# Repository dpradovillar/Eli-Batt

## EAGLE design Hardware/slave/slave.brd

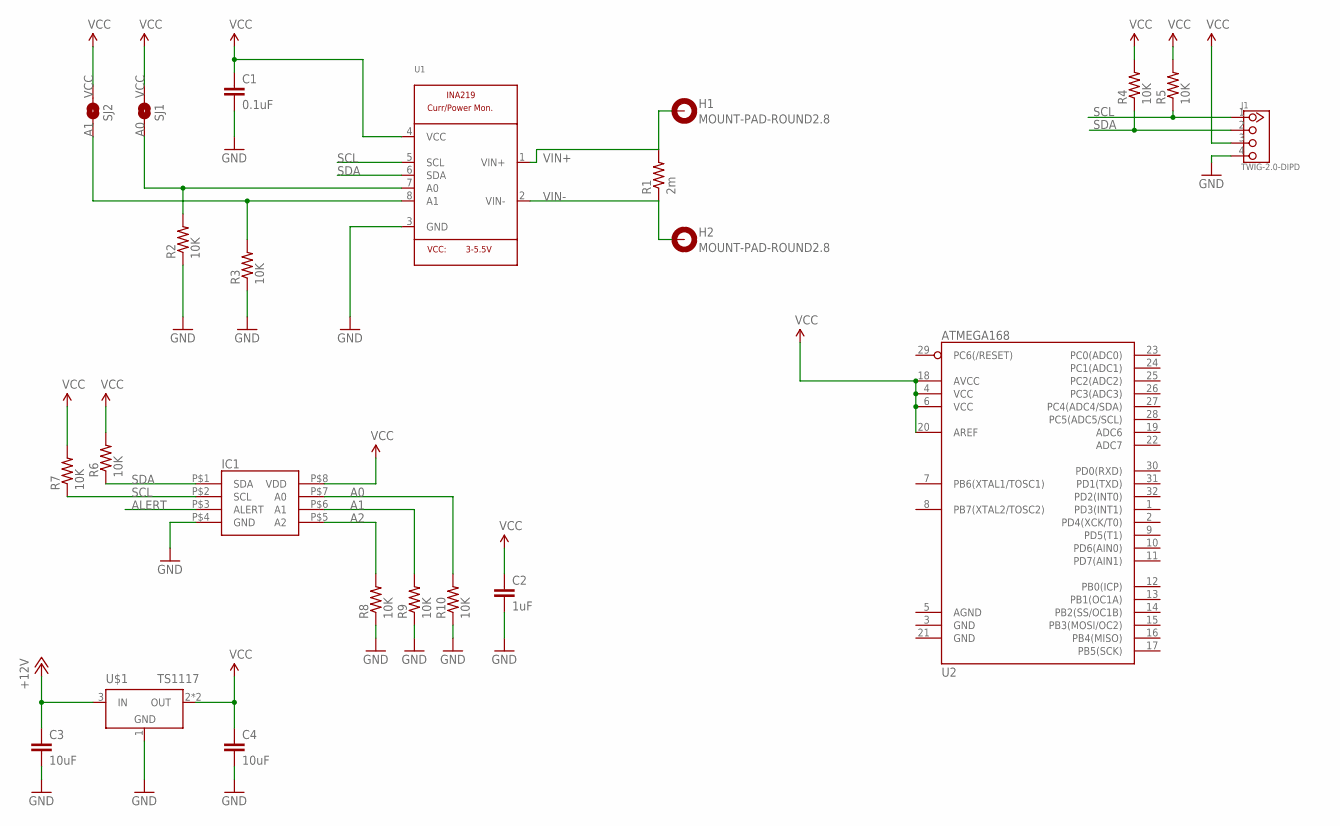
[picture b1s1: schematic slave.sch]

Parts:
C1: 0.1uF; 0805
C2: 1uF; 0805
C3, C4: 10uF; 0805
H1, H2: MOUNT-PAD-ROUND2.8; 2,8-PAD
IC1: MPC9804; MSOP-8
J1: TWIG-2.0-DIPD; 2.0_1X4_90
R1: 2m; R2512
R2, R3, R4, R5, R6, R7, R8, R9, R10: 10K; 0805
SJ1, SJ2: SOLDERJUMPERNO; SJ_2S-NO
U1: INA219; SOT23-8
U2: ATMEGA168; TQFP32-08
U$1: TS1117; SOT223

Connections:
+12V: C3.1, U$1.3 (IN)
A0: IC1.P$7 (A0), R2.2, R10.2, SJ1.1, U1.7 (A0)
A1: IC1.P$6 (A1), R3.2, R9.2, SJ2.1, U1.8 (A1)
A2: IC1.P$5 (A2), R8.2
ALERT: IC1.P$3 (ALERT)
GND: C1.2, C2.2, C3.2, C4.2, IC1.P$4 (GND), J1.4, R2.1, R3.1, R8.1, R9.1, R10.1, U1.3 (GND), U$1.1 (GND)
SCL: IC1.P$2 (SCL), J1.1, R5.1, R7.1, U1.5 (SCL)
SDA: IC1.P$1 (SDA), J1.2, R4.1, R6.1, U1.6 (SDA)
VCC: C1.1, C2.1, C4.1, IC1.P$8 (VDD), J1.3, R4.2, R5.2, R6.2, R7.2, SJ1.2, SJ2.2, U1.4 (VCC), U2.4 (VCC), U2.6 (VCC), U2.18 (AVCC), U2.20 (AREF), U$1.2 (OUT), U$1.4 (OUT)
VIN+: H1.B2,8, R1.2, U1.1 (VIN+)
VIN-: H2.B2,8, R1.1, U1.2 (VIN-)

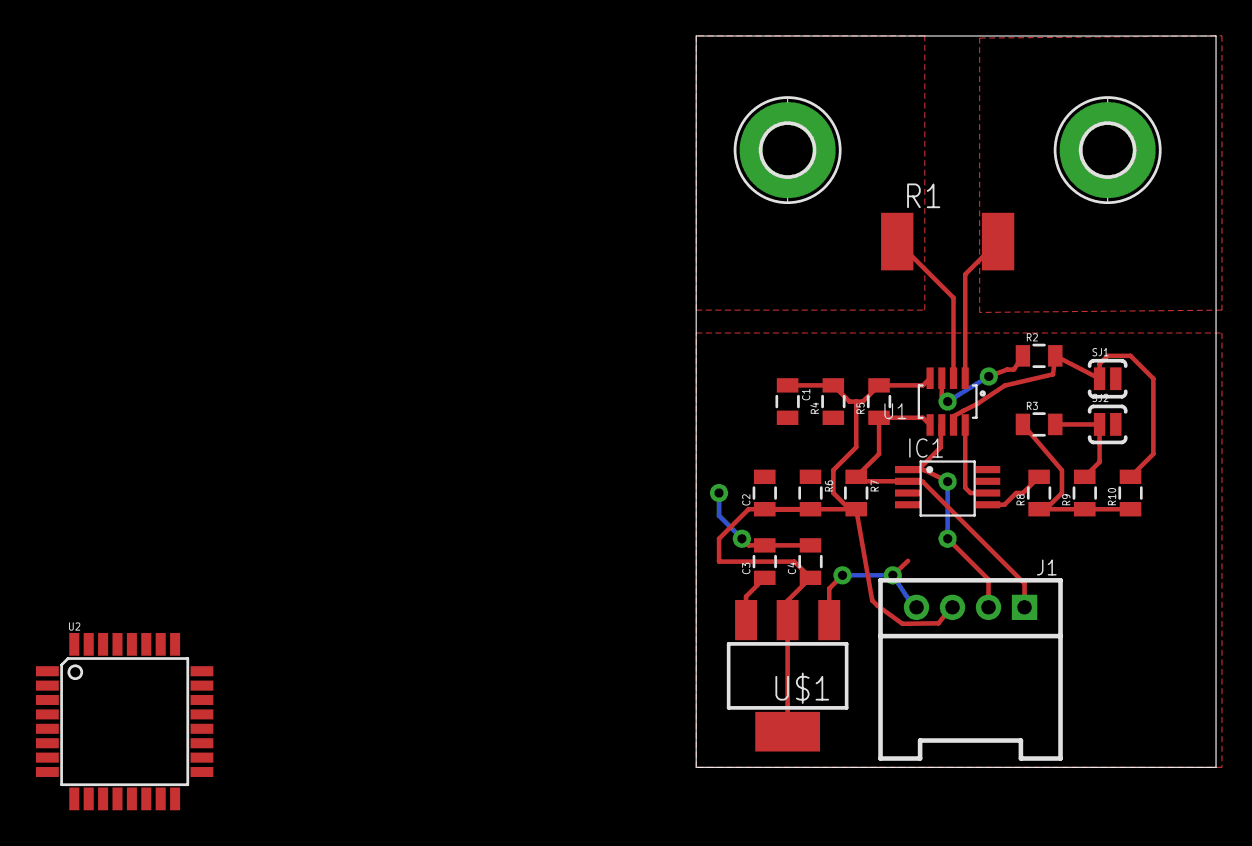
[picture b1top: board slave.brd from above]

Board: 2 copper layers, 28.9 x 40.6 mm, 23 parts (0 on the bottom side), 10 nets.

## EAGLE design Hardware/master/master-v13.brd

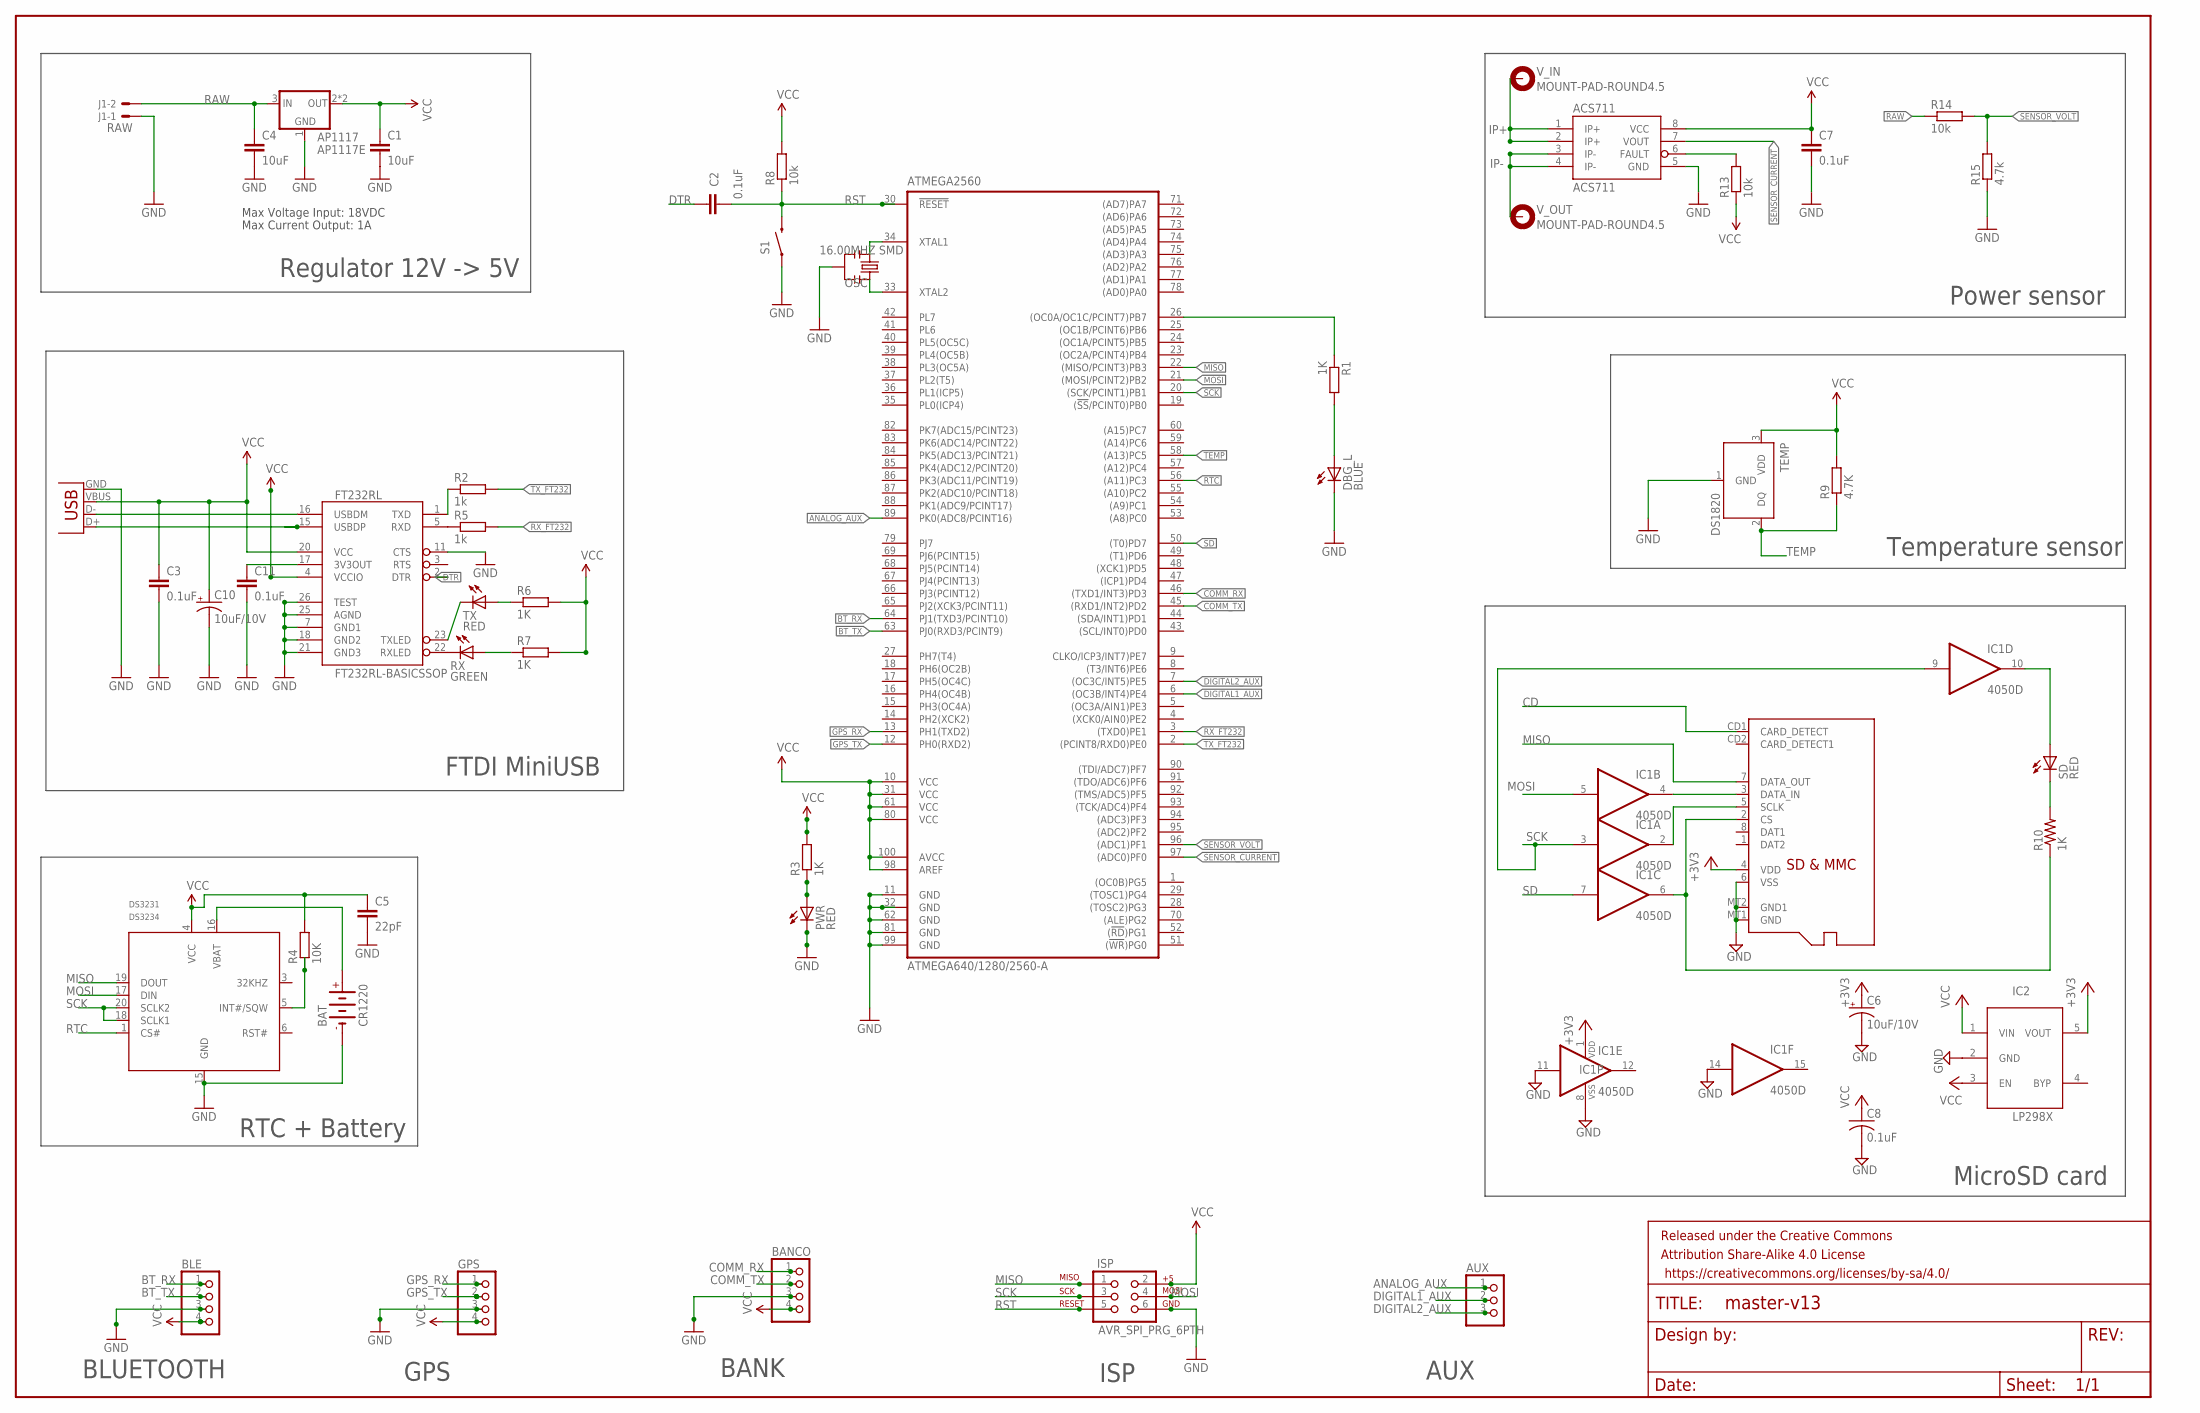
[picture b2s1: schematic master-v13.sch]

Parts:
ACS711: ACS711; SOIC8; MPN ACS711KLCTR-25AB-T
AP1117: AP1117E; SOT223; MPN AP1117E50G-13
ATMEGA2560: ATMEGA640/1280/2560-A; TQFP100A
AUX: PINHD-1X3; 1X03
BANCO: PINHD-1X4; 1X04
BAT: CR1220; MPN CR1220
BLE: PINHD-1X4; 1X04
C1, C4: 10uF; C0805K; MPN 0805ZD106KAT2A
C2, C7, C8: 0.1uF; C0805K; MPN MC0603B104K500CT
C3, C11: 0.1uF; 0402-CAP; MPN MC0603B104K500CT
C5: 22pF; 0402-CAP; MPN MC0603B104K500CT
C6, C10: 10uF/10V; A/3216-18R; MPN TAJP106M010RNJ
DBG_L: BLUE; CHIPLED_0805; MPN 150080BS75000
DS3231: DS3234; SO-20DW
FRAME1: FRAME-LEDGER; CREATIVE_COMMONS
FT232RL: FT232RL-BASICSSOP; SSOP28DB
GPS: PINHD-1X4; 1X04
IC1: 4050D; SO16; MPN 74HC4050D,653
IC2: LP298XS; SOT23-5L
ISP: AVR_SPI_PRG_6PTH; 2X3
J1: RAW; 7395-02
OSC: 16.00MHZ SMD; RESONATOR-SMD; MPN PBRC8.00HR50X000
PWR: RED; CHIPLED_0805; MPN KPT-2012SRC-J4
R1, R3, R6, R7, R10: 1K; R0805; MPN CRCW08051K00FKTA
R2, R5: 1k; R0805; MPN CRCW08051K00FKTA
R4: 10K; R0805; MPN CRCW08051K00FKTA
R8, R13, R14: 10k; R0805; MPN CRCW080510K0FKTA
R9: 4.7K; R0805; MPN CRCW080510K0FKTA
R15: 4.7k; R0805; MPN CRCW08053K30FKTA
RX: GREEN; CHIPLED_0805; MPN 150080VS75000
S1: SWITCH-MOMENTARY-2-SMD-1101NE; TACTILE-SWITCH-1101NE
SD: RED; CHIP-LED0805
TEMP: DS1820; TO-92; MPN MCP9808-E/MS
TX: RED; CHIPLED_0805; MPN KPT-2012SRC-J4
V_IN: MOUNT-PAD-ROUND4.5; 4,5-PAD
V_OUT: MOUNT-PAD-ROUND4.5; 4,5-PAD
X1: USB-MB-H
X2: MICROSD; MPN 2908-05WB-MG

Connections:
+3V3: C6.+, IC1.1 (VDD), IC2.5 (VOUT), X2.4 (VDD)
ANALOG_AUX: ATMEGA2560.89 (PK0(ADC8/PCINT16)), AUX.1
BT_RX: ATMEGA2560.64 (PJ1(TXD3/PCINT10)), BLE.1
BT_TX: ATMEGA2560.63 (PJ0(RXD3/PCINT9)), BLE.2
CD: X2.CD1 (CARD_DETECT)
COMM_RX: ATMEGA2560.46 ((TXD1/INT3)PD3), BANCO.1
COMM_TX: ATMEGA2560.45 ((RXD1/INT2)PD2), BANCO.2
DIGITAL1_AUX: ATMEGA2560.6 ((OC3B/INT4)PE4), AUX.2
DIGITAL2_AUX: ATMEGA2560.7 ((OC3C/INT5)PE5), AUX.3
DTR: C2.2, FT232RL.2 (DTR)
GND: ACS711.5 (GND), AP1117.1 (GND), ATMEGA2560.11 (GND), ATMEGA2560.32 (GND), ATMEGA2560.62 (GND), ATMEGA2560.81 (GND), ATMEGA2560.99 (GND), BANCO.3, BAT.-, BLE.3, C1.2, C3.2, C4.2, C5.2, C6.-, C7.2, C8.2, C10.-, C11.2, DBG_L.C, DS3231.15 (GND), FT232RL.7 (GND1), FT232RL.11 (CTS), FT232RL.18 (GND2), FT232RL.21 (GND3), FT232RL.25 (AGND), FT232RL.26 (TEST), GPS.3, IC1.8 (VSS), IC1.11 (I), IC1.14 (I), IC2.2 (GND), ISP.6, J1.1, OSC.2, PWR.C, R15.1, S1.P$1 (1), TEMP.1 (GND), X1.GND, X2.6 (VSS), X2.MT1 (GND), X2.MT2 (GND1)
GPS_RX: ATMEGA2560.13 (PH1(TXD2)), GPS.1
GPS_TX: ATMEGA2560.12 (PH0(RXD2)), GPS.2
IP+: ACS711.1 (IP+), ACS711.2 (IP+), V_IN.B4,5
IP-: ACS711.3 (IP-), ACS711.4 (IP-), V_OUT.B4,5
MISO: ATMEGA2560.22 ((MISO/PCINT3)PB3), DS3231.19 (DOUT), ISP.1, X2.7 (DATA_OUT)
MOSI: ATMEGA2560.21 ((MOSI/PCINT2)PB2), DS3231.17 (DIN), IC1.5 (I), ISP.4
unnamed: BAT.+, DS3231.16 (VBAT)
unnamed: ATMEGA2560.34 (XTAL1), OSC.1
unnamed: DBG_L.A, R1.2
unnamed: ATMEGA2560.26 ((OC0A/OC1C/PCINT7)PB7), R1.1
unnamed: PWR.A, R3.1
unnamed: FT232RL.1 (TXD), R2.1
unnamed: DS3231.5 (INT#/SQW), R4.1
unnamed: FT232RL.5 (RXD), R5.1
unnamed: IC1.10 (O), SD.A
unnamed: FT232RL.22 (RXLED), RX.C
unnamed: R7.1, RX.A
unnamed: FT232RL.23 (TXLED), TX.C
unnamed: R6.1, TX.A
unnamed: ATMEGA2560.33 (XTAL2), OSC.3
unnamed: IC1.2 (O), X2.5 (SCLK)
unnamed: IC1.6 (O), R10.1, X2.2 (CS)
unnamed: R10.2, SD.C
unnamed: IC1.4 (O), X2.3 (DATA_IN)
unnamed: C11.1, FT232RL.17 (3V3OUT)
unnamed: ACS711.6 (FAULT), R13.2
RAW: AP1117.3 (IN), C4.1, J1.2, R14.1
RST: ATMEGA2560.30 (!RESET!), C2.1, ISP.5, R8.1, S1.P$2 (2)
RTC: ATMEGA2560.56 ((A11)PC3), DS3231.1 (CS#)
RX_FT232: ATMEGA2560.3 ((TXD0)PE1), R5.2
SCK: ATMEGA2560.20 ((SCK/PCINT1)PB1), DS3231.18 (SCLK1), DS3231.20 (SCLK2), IC1.3 (I), IC1.9 (I), ISP.3
SD: ATMEGA2560.50 ((T0)PD7), IC1.7 (I)
SENSOR_CURRENT: ACS711.7 (VOUT), ATMEGA2560.97 ((ADC0)PF0)
SENSOR_VOLT: ATMEGA2560.96 ((ADC1)PF1), R14.2, R15.2
TEMP: ATMEGA2560.58 ((A13)PC5), R9.1, TEMP.2 (DQ)
TX_FT232: ATMEGA2560.2 ((PCINT8/RXD0)PE0), R2.2
USB_D+1: FT232RL.15 (USBDP), X1.D+
USB_D-1: FT232RL.16 (USBDM), X1.D-
VCC: ACS711.8 (VCC), AP1117.2 (OUT), AP1117.4 (OUT), ATMEGA2560.10 (VCC), ATMEGA2560.31 (VCC), ATMEGA2560.61 (VCC), ATMEGA2560.80 (VCC), ATMEGA2560.98 (AREF), ATMEGA2560.100 (AVCC), BANCO.4, BLE.4, C1.1, C3.1, C5.1, C7.1, C8.1, C10.+, DS3231.4 (VCC), FT232RL.4 (VCCIO), FT232RL.20 (VCC), GPS.4, IC2.1 (VIN), IC2.3 (EN), ISP.2, R3.2, R4.2, R6.2, R7.2, R8.2, R9.2, R13.1, TEMP.3 (VDD), X1.VBUS

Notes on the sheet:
Max Voltage Input: 18VDC
Max Current Output: 1A
Regulator 12V -> 5V
RTC + Battery
Power sensor
Temperature sensor
FTDI MiniUSB
MicroSD card
BANK
GPS
BLUETOOTH
ISP
AUX

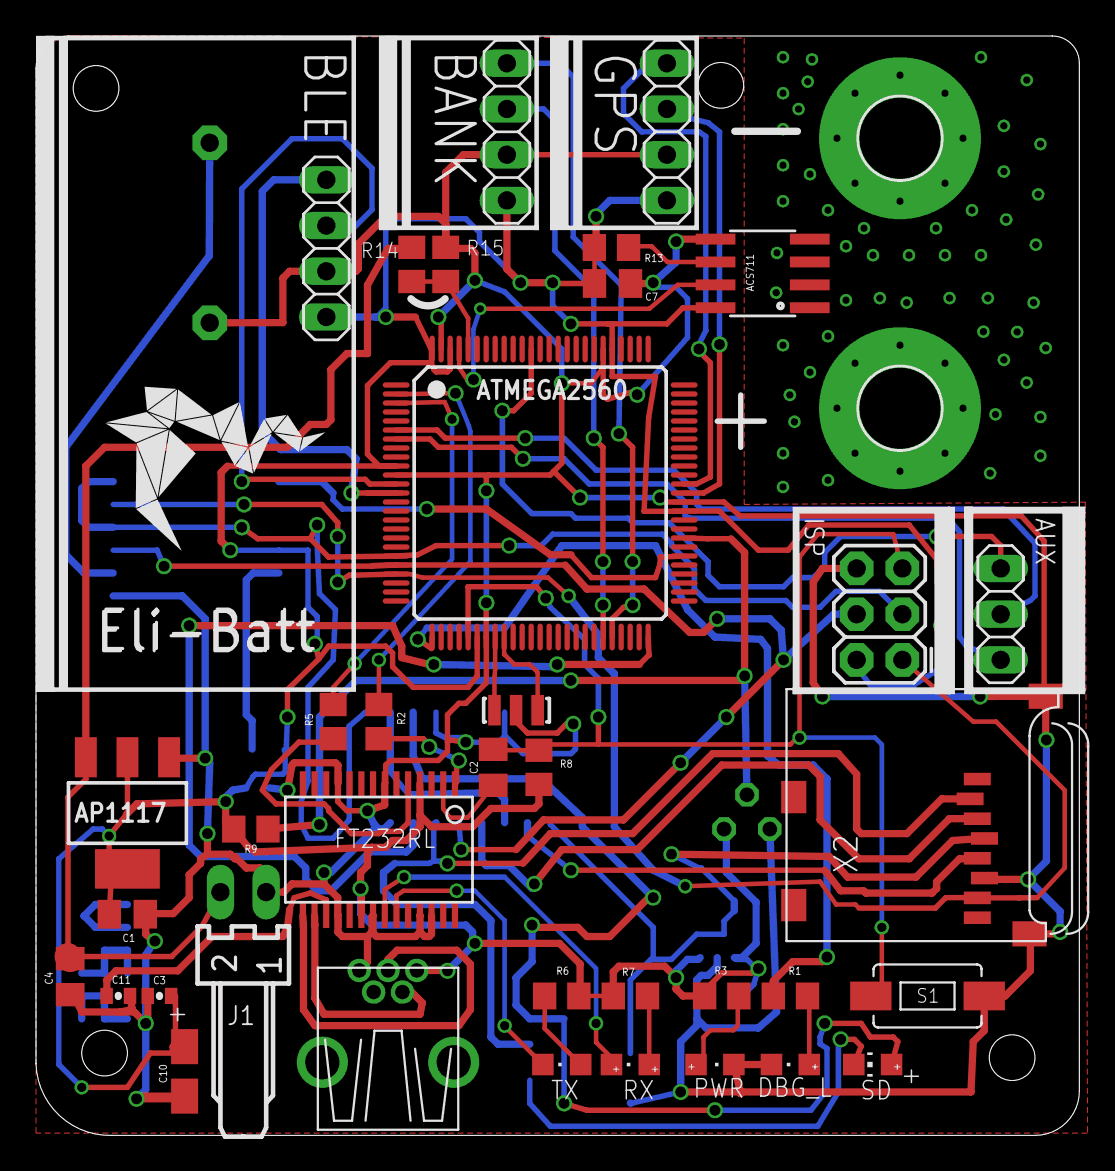
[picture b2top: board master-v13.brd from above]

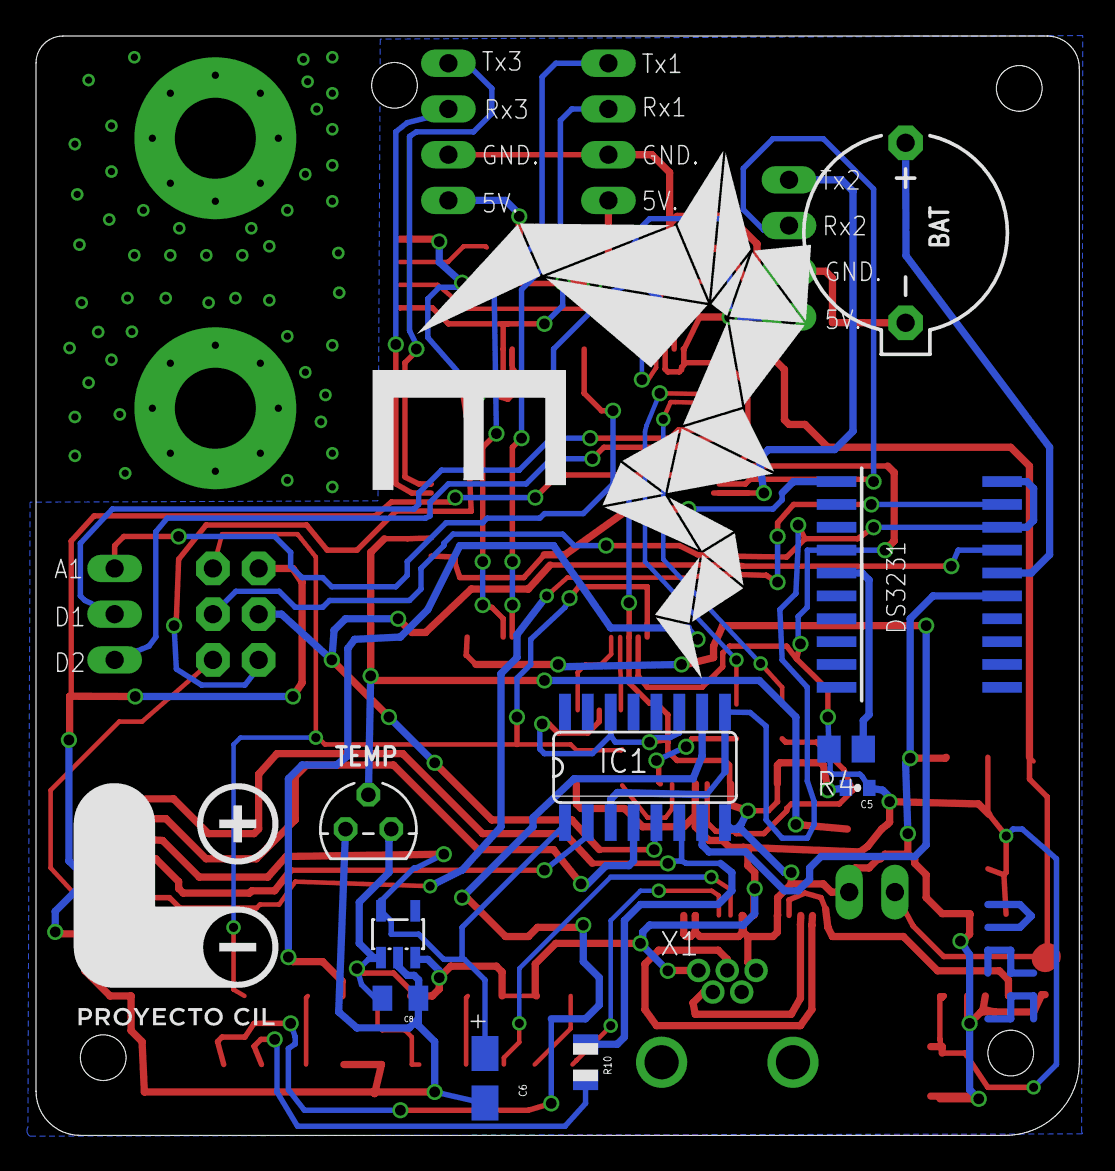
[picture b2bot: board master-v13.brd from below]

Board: 2 copper layers, 58.0 x 61.1 mm, 53 parts (13 on the bottom side), 49 nets.

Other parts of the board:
U$1: LOGO_CIL
U$2: LOGO_ELIBATT
U$4: LOGO_ELIBATT2

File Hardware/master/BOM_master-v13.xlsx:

Qty | Value | Device | Package | Ref | Description | Price | Total Price | Manuf. Part | Manufature | Link/Supplier |  |  |  |  |  |  |  |  | .
5 | 0.1uF | C-EUC0805K | C0805K | C2, C3, C7, C8, C11 | CAPACITOR, European symbol | 0.1 | 0.1 | CL21F104ZBCNNNC | Samsung Electro-Mechanics | http://www.digikey.com/product-detail/en/CL21F104ZBCNNNC/127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 |  |  |  |  |  |  |  |  | .
4 | 10uF | C-EUC0805K | C0805K | C1, C4, C6, C10 | CAPACITOR, European symbol | 0.16 | 0.32 | CC0805ZKY5V6BB106 | Yageo | http://www.digikey.com/product-detail/en/CC0805ZKY5V6BB106/3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 |  |  |  |  |  |  |  |  | .
1 | 22pF | C-EUC0805K | C0805K | C5 | CAPACITOR, European symbol | 0.16 | 0.32 |  |  |  |  |  |  |  |  |  |  |  | .
4 | 10k | R-EU_R0805 | R0805 | R4, R8, R13, R14 | RESISTOR, European symbol | 0.18 | 0.89999999999999991 | RC0805JR-0710KL | Yageo | http://www.digikey.com/product-detail/en/RC0805JR-0710KL/311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 |  |  |  |  |  |  |  |  | .
7 | 1K | R-EU_R0805 | R0805 | R1, R2, R3, R5, R6, R7, R10 | RESISTOR, European symbol | 0.1 | 0.2 | RC0805JR-071KL | Yageo | http://www.digikey.com/product-detail/en/RC0805JR-071KL/311-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 |  |  |  |  |  |  |  |  | .
2 | 4.7K | R-EU_R0805 | R0805 | R9, R15 | RESISTOR, European symbol | 0.1 | 0.2 | RC0805JR-074K7L | yageo |  |  |  |  |  |  |  |  |  | .
1 | J1 | J1 | J1 | J1 | CONN HEADER 2POS .100 R/A TIN | 0.32 | 0.32 | 2205321 | Molex | http://www.digikey.com/product-detail/en/0022053021/WM4300-N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 |  |  |  |  |  |  |  |  | .
1 | 16.00MHZ SMD | RESONATOR-SMD | RESONATOR-SMD | OSC 16MHZ | Resonator | 0.48 | 0.48 | CSTCE16M0V53-R0 | Murata | http://www.digikey.com/product-detail/en/CSTCE16M0V53-R0/490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 |  |  |  |  |  |  |  |  | .
1 | ACS711 | ACS711 | SOIC8 | ACS711 | Hall-effect-based isolated linear current sensor | 3.05 | 3.05 | ACS711KLCTR-25AB-T | Allegro MicroSystems | http://www.digikey.com/product-detail/en/ACS711KLCTR-25AB-T/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 |  |  |  |  |  |  |  |  | .
1 | AP1117E | AP1117E | SOT223 | 5V | LDO Regulator | 0.41 | 0.41 | AP1117IE50G-13 | Diodes Incorporated | http://www.digikey.com/product-detail/en/AP1117E50G-13/AP111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 |  |  |  |  |  |  |  |  | .
1 | ATMEGA2560-16AU | ATMEGA2560 | TQFP100A | ATMEGA2560 | MICROCONTROLLER | 16.72 | 16.72 | ATMEGA2560-16AU | Atmel | http://www.digikey.com/product-detail/en/ATMEGA2560-16AU/ATM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 |  |  |  |  |  |  |  |  | .
1 | CR1220 | CR1220 | CR1220 | BAT | LI BATTERY Panasonic | 1.29 | 1.2 | CR-1220/HFN | Panasonic | http://www.digikey.com/product-detail/en/CR-1220%2FHFN/P244-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 |  |  |  |  |  |  |  |  | .
1 | DS3234 | DS3234 | 20-SOIC | DS3234 | RTC | 8.9 | 8.9 | DS3234S#T&R | Maxim Integrated | http://www.digikey.com/product-detail/en/DS3234S%23T%26R/DS3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 |  |  |  |  |  |  |  |  | .
1 | FT232RL-BASICSSOP | FT232RL | 28-SSOP | FT232RL | USB UART | 4.5 | 4.5 | FT232RL-REEL | FTDI | http://www.digikey.com/product-detail/en/FT232RL-REEL/768-10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 |  |  |  |  |  |  |  |  | .
1 | 4050D | 4050M | 16-SOIC | IC1 | Buffer/Line Driver | 0.56999999999999995 | 0.56999999999999995 | CD74HC4050M | Texas Instruments | http://www.digikey.com/product-detail/en/CD74HC4050M/296-921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 |  |  |  |  |  |  |  |  | .
1 | LP298XS | MCP1711T-33I | 5SOT23 | IC2 | REG LDO 3.3V | 0.44 | 0.44 | MCP1711T-33I/OT | Microchip | http://www.digikey.com/product-detail/en/MCP1711T-33I%2FOT/M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 |  |  |  |  |  |  |  |  | .
1 | DS1820 | DS1820 | TO-92 | Temp | TEMP SENSOR | 2.99 | 2.99 | DS18S20+ | Maxim Integrated | http://www.digikey.com/product-detail/en/DS18S20%2B/DS18S20%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 |  |  |  |  |  |  |  |  | .
1 | BLUE | LEDCHIPLED_0805 | CHIPLED_0805 | DBG_L | LED | 0.44 | 0.44 | LTST-C171TBKT | Lite-On Inc | http://www.digikey.com/product-detail/en/LTST-C171TBKT/160-1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 |  |  |  |  |  |  |  |  | .
1 | GREEN | LEDCHIPLED_0805 | CHIPLED_0805 | RX | LED | 0.3 | 0.3 | LTST-C171GKT | Lite-On Inc | http://www.digikey.com/product-detail/en/LTST-C171GKT/160-14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 |  |  |  |  |  |  |  |  | .
3 | RED | LEDCHIPLED_0805 | CHIPLED_0805 | PWR, TX, SD | LED | 0.08 | 0.08 | LH R974-LP-1 | OSRAM Opto | http://www.digikey.com/product-detail/en/LH%20R974-LP-1/475-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 |  |  |  |  |  |  |  |  | .
1 | MOMENTARY-2-SMD | SWITCH | TACTILE-SWITCH-1101NE | S1 | Various NO switches- pushbuttons, reed, etc | 7.0000000000000007E-2 | 7.0000000000000007E-2 | IM120731002 | Itead | http://imall.iteadstudio.com/electronic-components/button-an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 |  |  |  |  |  |  |  |  | .
1 | USB-MB-H | USB-MB-H | USB-MB-H | JP1 | USB Connectors | 2.2799999999999998 | 2.2799999999999998 | 565790519 | Molex | http://www.digikey.com/product-detail/en/0565790519/WM17121-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 |  |  |  |  |  |  |  |  | .
1 | MICROSD | USD-SOCKETNEW | MICRO-SD-SOCKET-PP | MICROSD | microSD Socket | 1.82 | 1.82 | 101-00660-68-6 | Amphenol | http://www.digikey.com/product-detail/en/101-00660-68-6/101-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 |  |  |  |  |  |  |  |  | .
 |  |  |  |  |  |  |  |  |  |  |  |  |  |  |  |  |  |  | .
 |  |  |  |  |  | TOTAL | 44.789999999999992 |  |  |  |  |  |  |  |  |  |  |  | .
 |  |  |  |  |  |  |  |  |  |  |  |  |  |  |  |  |  |  | .
 |  |  |  |  |  |  |  |  |  |  |  |  |  |  |  |  |  |  | .
 |  |  |  |  |  |  |  |  |  |  |  |  |  |  |  |  |  |  | .
 |  |  |  |  |  |  |  |  |  |  |  |  |  |  |  |  |  |  | .
 |  |  |  |  |  |  |  |  |  |  |  |  |  |  |  |  |  |  | .

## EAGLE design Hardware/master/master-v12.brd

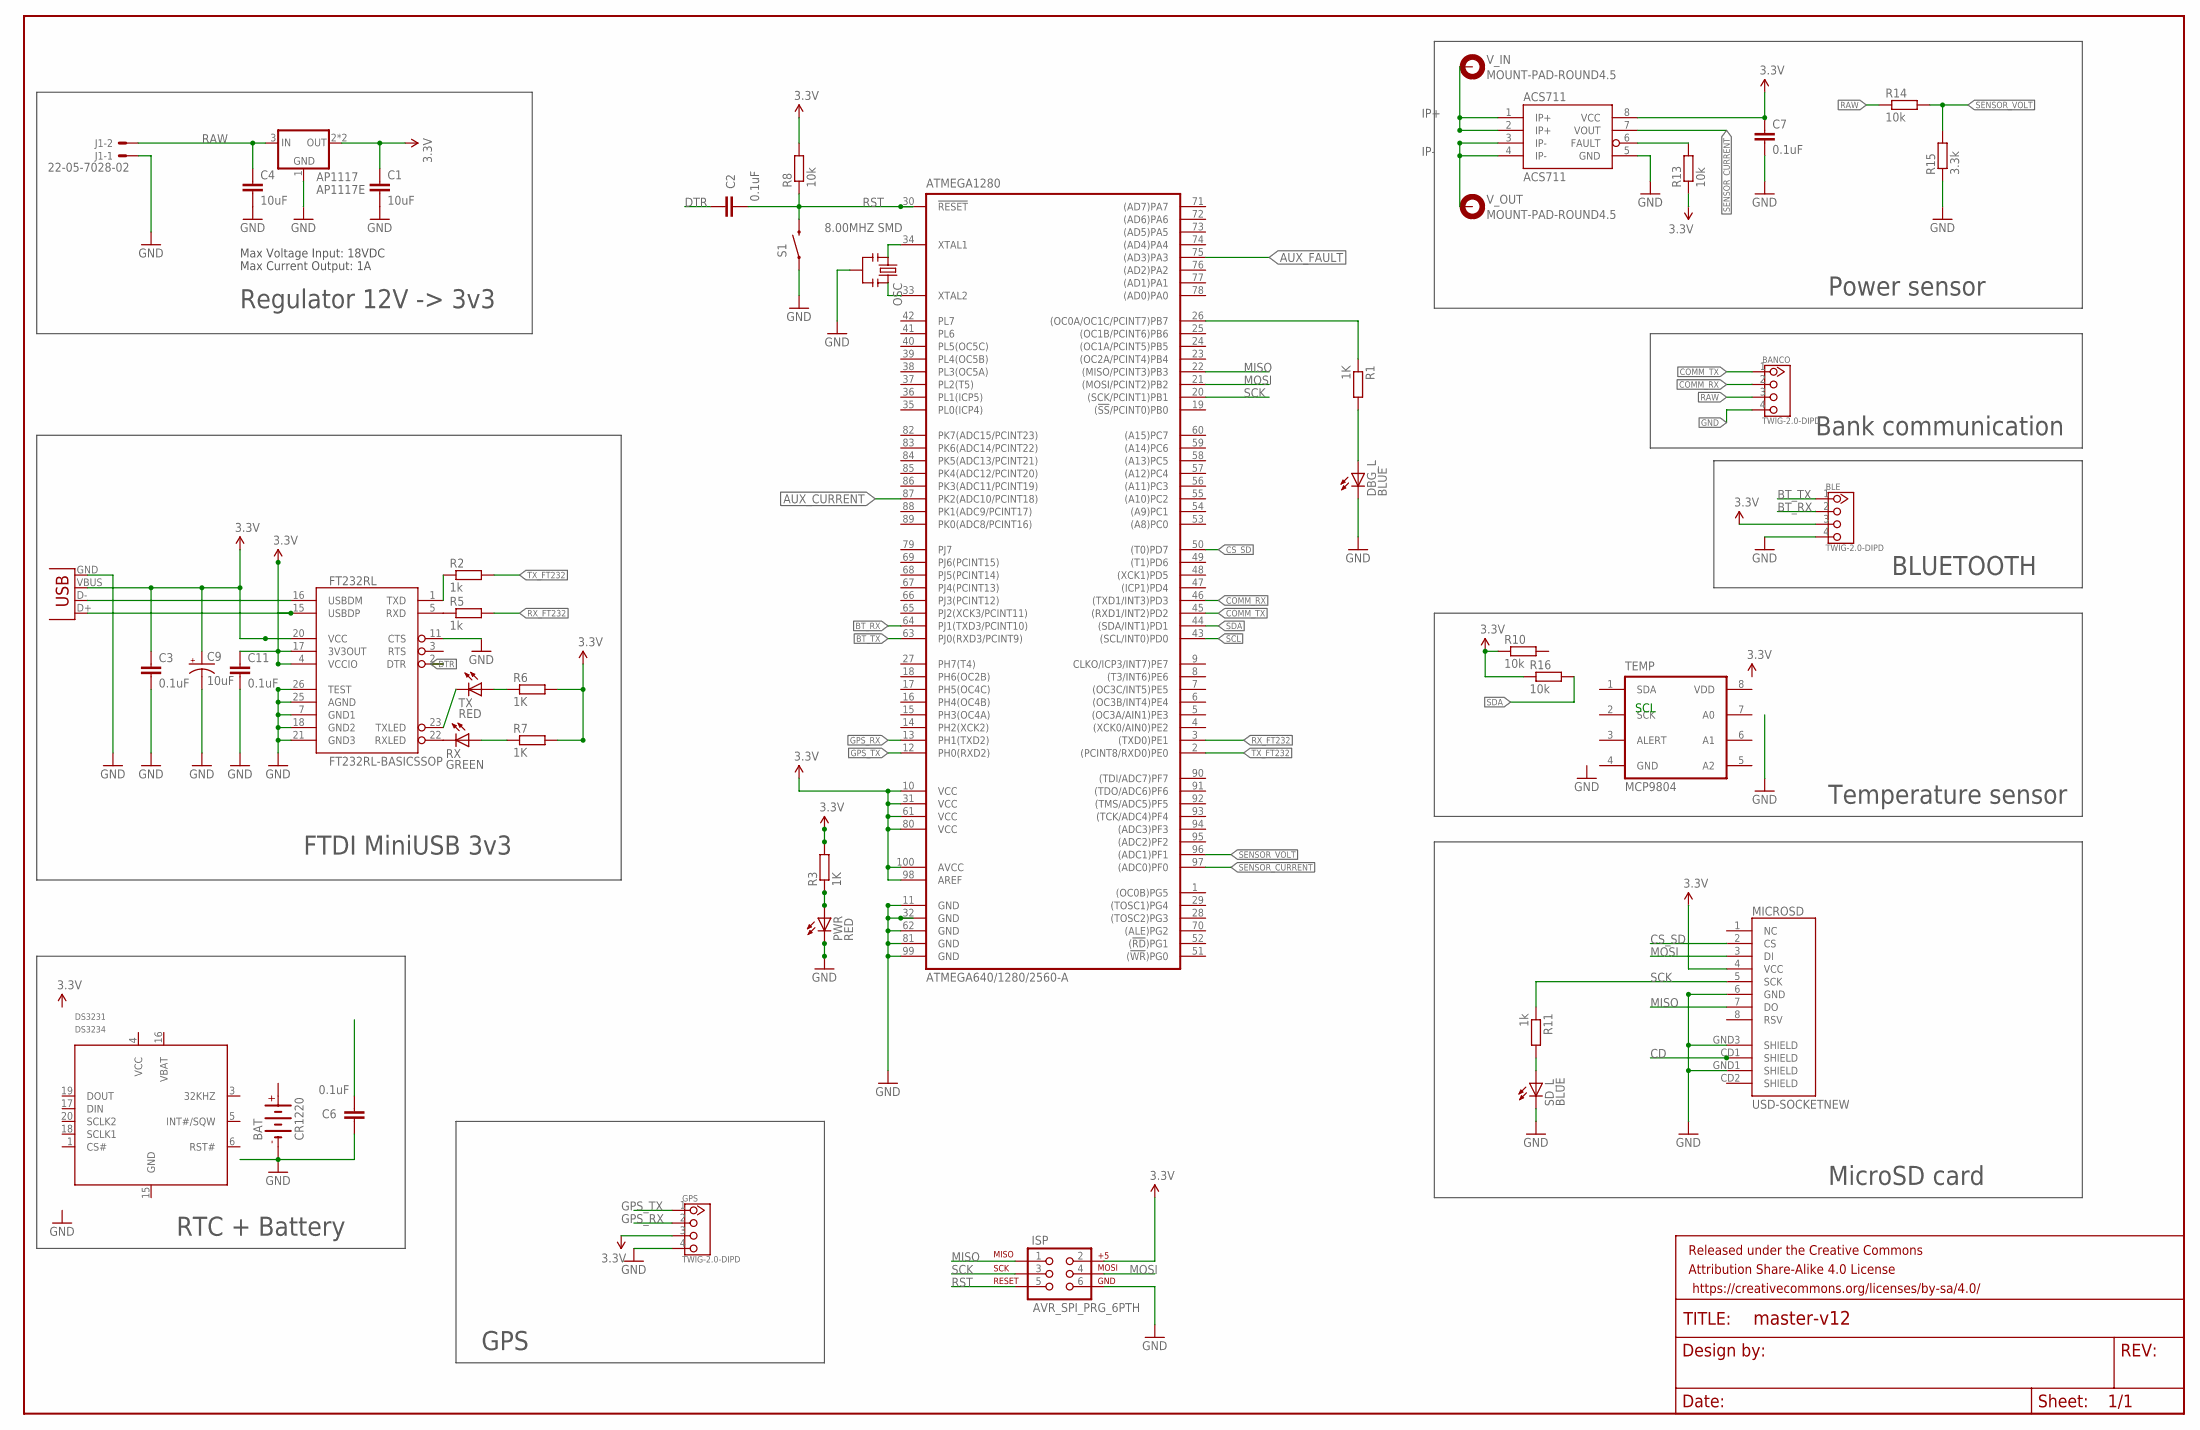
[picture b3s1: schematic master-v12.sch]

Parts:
ACS711: ACS711; SOIC8; MPN ACS711KLCTR-25AB-T
AP1117: AP1117E; SOT223; MPN AP1117E33G-13
ATMEGA1280: ATMEGA640/1280/2560-A; TQFP100A
BANCO: TWIG-2.0-DIPD; 2.0_1X4_90
BAT: CR1220; MPN CR1220
BLE: TWIG-2.0-DIPD; 2.0_1X4_90
C1, C4: 10uF; C0805K; MPN 0805ZD106KAT2A
C2, C6, C7: 0.1uF; C0805K; MPN MC0603B104K500CT
C3, C11: 0.1uF; 0402-CAP; MPN MC0603B104K500CT
C9: 10uF; EIA3216; MPN 0805ZD106KAT2A
DBG_L: BLUE; CHIPLED_0805; MPN 150080BS75000
DS3231: DS3234; SO-20DW
FRAME1: FRAME-LEDGER; CREATIVE_COMMONS
FT232RL: FT232RL-BASICSSOP; SSOP28DB
GPS: TWIG-2.0-DIPD; 2.0_1X4_90
ISP: AVR_SPI_PRG_6PTH; 2X3
J1: 22-05-7028-02; 7395-02
MICROSD: USD-SOCKETNEW; MICRO-SD-SOCKET-PP
OSC: 8.00MHZ SMD; RESONATOR-SMD; MPN PBRC8.00HR50X000
PWR: RED; CHIPLED_0805; MPN KPT-2012SRC-J4
R1, R3, R6, R7: 1K; R0805; MPN CRCW08051K00FKTA
R2, R5, R11: 1k; R0805; MPN CRCW08051K00FKTA
R8, R10, R13, R14, R16: 10k; R0805; MPN CRCW080510K0FKTA
R15: 3.3k; R0805; MPN CRCW08053K30FKTA
RX: GREEN; CHIPLED_0805; MPN 150080VS75000
S1: SWITCH-MOMENTARY-2-SMD-1101NE; TACTILE-SWITCH-1101NE
SD_L: BLUE; CHIPLED_0805; MPN 150080BS75000
TEMP: MCP9804; MSOP8; MPN MCP9808-E/MS
TX: RED; CHIPLED_0805; MPN KPT-2012SRC-J4
V_IN: MOUNT-PAD-ROUND4.5; 4,5-PAD
V_OUT: MOUNT-PAD-ROUND4.5; 4,5-PAD
X1: USB-MB-H

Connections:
3.3V: ACS711.8 (VCC), ATMEGA1280.10 (VCC), ATMEGA1280.31 (VCC), ATMEGA1280.61 (VCC), ATMEGA1280.80 (VCC), ATMEGA1280.98 (AREF), ATMEGA1280.100 (AVCC), BLE.3, C7.1, C11.1, FT232RL.4 (VCCIO), FT232RL.17 (3V3OUT), GPS.3, ISP.2, MICROSD.4 (VCC), R3.2, R6.2, R7.2, R8.2, R10.1, R13.1, R16.1
AUX_CURRENT: ATMEGA1280.87 (PK2(ADC10/PCINT18))
AUX_FAULT: ATMEGA1280.75 ((AD3)PA3)
BT_RX: ATMEGA1280.64 (PJ1(TXD3/PCINT10)), BLE.2
BT_TX: ATMEGA1280.63 (PJ0(RXD3/PCINT9)), BLE.1
CD: MICROSD.CD1 (SHIELD)
COMM_RX: ATMEGA1280.46 ((TXD1/INT3)PD3), BANCO.2
COMM_TX: ATMEGA1280.45 ((RXD1/INT2)PD2), BANCO.1
CS_SD: ATMEGA1280.50 ((T0)PD7), MICROSD.2 (CS)
DTR: C2.2, FT232RL.2 (DTR)
GND: ACS711.5 (GND), AP1117.1 (GND), ATMEGA1280.11 (GND), ATMEGA1280.32 (GND), ATMEGA1280.62 (GND), ATMEGA1280.81 (GND), ATMEGA1280.99 (GND), BANCO.4, BAT.-, BLE.4, C1.2, C3.2, C4.2, C6.2, C7.2, C9.C (-), C11.2, DBG_L.C, FT232RL.7 (GND1), FT232RL.11 (CTS), FT232RL.18 (GND2), FT232RL.21 (GND3), FT232RL.25 (AGND), FT232RL.26 (TEST), GPS.4, ISP.6, J1.1, MICROSD.6 (GND), MICROSD.GND1 (SHIELD), MICROSD.GND3 (SHIELD), OSC.2, PWR.C, R15.1, S1.P$1 (1), SD_L.C, TEMP.4 (GND), X1.GND
GPS_RX: ATMEGA1280.13 (PH1(TXD2)), GPS.2
GPS_TX: ATMEGA1280.12 (PH0(RXD2)), GPS.1
IP+: ACS711.1 (IP+), ACS711.2 (IP+), V_IN.B4,5
IP-: ACS711.3 (IP-), ACS711.4 (IP-), V_OUT.B4,5
MISO: ATMEGA1280.22 ((MISO/PCINT3)PB3), ISP.1, MICROSD.7 (DO)
MOSI: ATMEGA1280.21 ((MOSI/PCINT2)PB2), ISP.4, MICROSD.3 (DI)
unnamed: ATMEGA1280.34 (XTAL1), OSC.1
unnamed: DBG_L.A, R1.2
unnamed: ATMEGA1280.26 ((OC0A/OC1C/PCINT7)PB7), R1.1
unnamed: PWR.A, R3.1
unnamed: FT232RL.1 (TXD), R2.1
unnamed: FT232RL.5 (RXD), R5.1
unnamed: FT232RL.22 (RXLED), RX.C
unnamed: R7.1, RX.A
unnamed: FT232RL.23 (TXLED), TX.C
unnamed: R6.1, TX.A
unnamed: ATMEGA1280.33 (XTAL2), OSC.3
unnamed: R11.2, SD_L.A
unnamed: ACS711.6 (FAULT), R13.2
RAW: AP1117.3 (IN), BANCO.3, C4.1, J1.2, R14.1
RST: ATMEGA1280.30 (!RESET!), C2.1, ISP.5, R8.1, S1.P$2 (2)
RX_FT232: ATMEGA1280.3 ((TXD0)PE1), R5.2
SCK: ATMEGA1280.20 ((SCK/PCINT1)PB1), ISP.3, MICROSD.5 (SCK), R11.1
SCL: ATMEGA1280.43 ((SCL/INT0)PD0)
SDA: ATMEGA1280.44 ((SDA/INT1)PD1), R16.2
SENSOR_CURRENT: ACS711.7 (VOUT), ATMEGA1280.97 ((ADC0)PF0)
SENSOR_VOLT: ATMEGA1280.96 ((ADC1)PF1), R14.2, R15.2
TX_FT232: ATMEGA1280.2 ((PCINT8/RXD0)PE0), R2.2
USB_D+1: FT232RL.15 (USBDP), X1.D+
USB_D-1: FT232RL.16 (USBDM), X1.D-
VCC: AP1117.2 (OUT), AP1117.4 (OUT), C1.1, C3.1, C9.A (+), FT232RL.20 (VCC), X1.VBUS
VDD: TEMP.8 (VDD)

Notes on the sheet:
Max Voltage Input: 18VDC
Max Current Output: 1A
Regulator 12V -> 3v3
RTC + Battery
Power sensor
Temperature sensor
FTDI MiniUSB 3v3
MicroSD card
Bank communication
GPS
BLUETOOTH
SCL

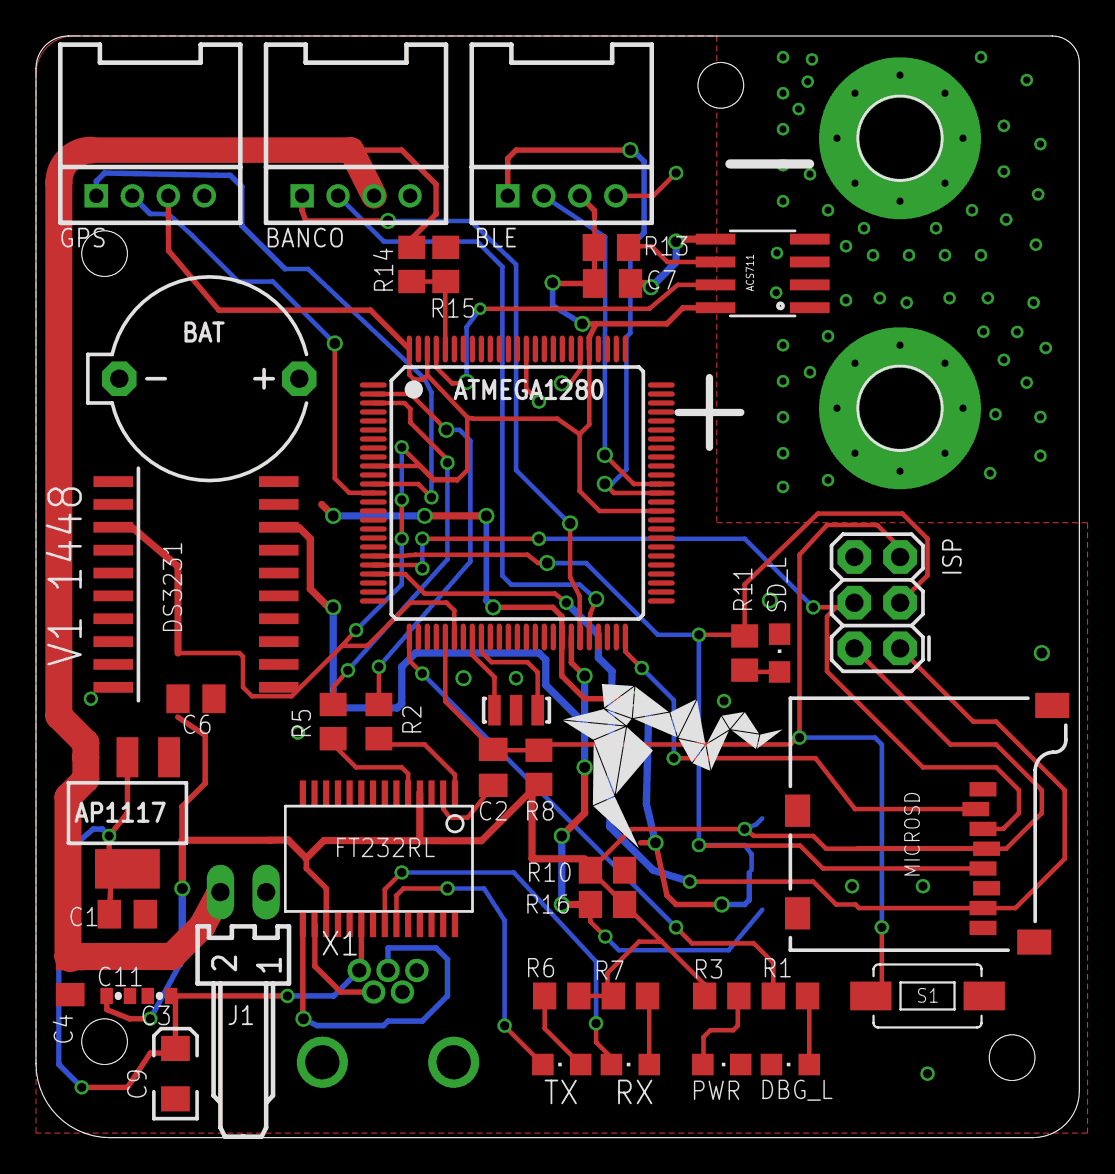
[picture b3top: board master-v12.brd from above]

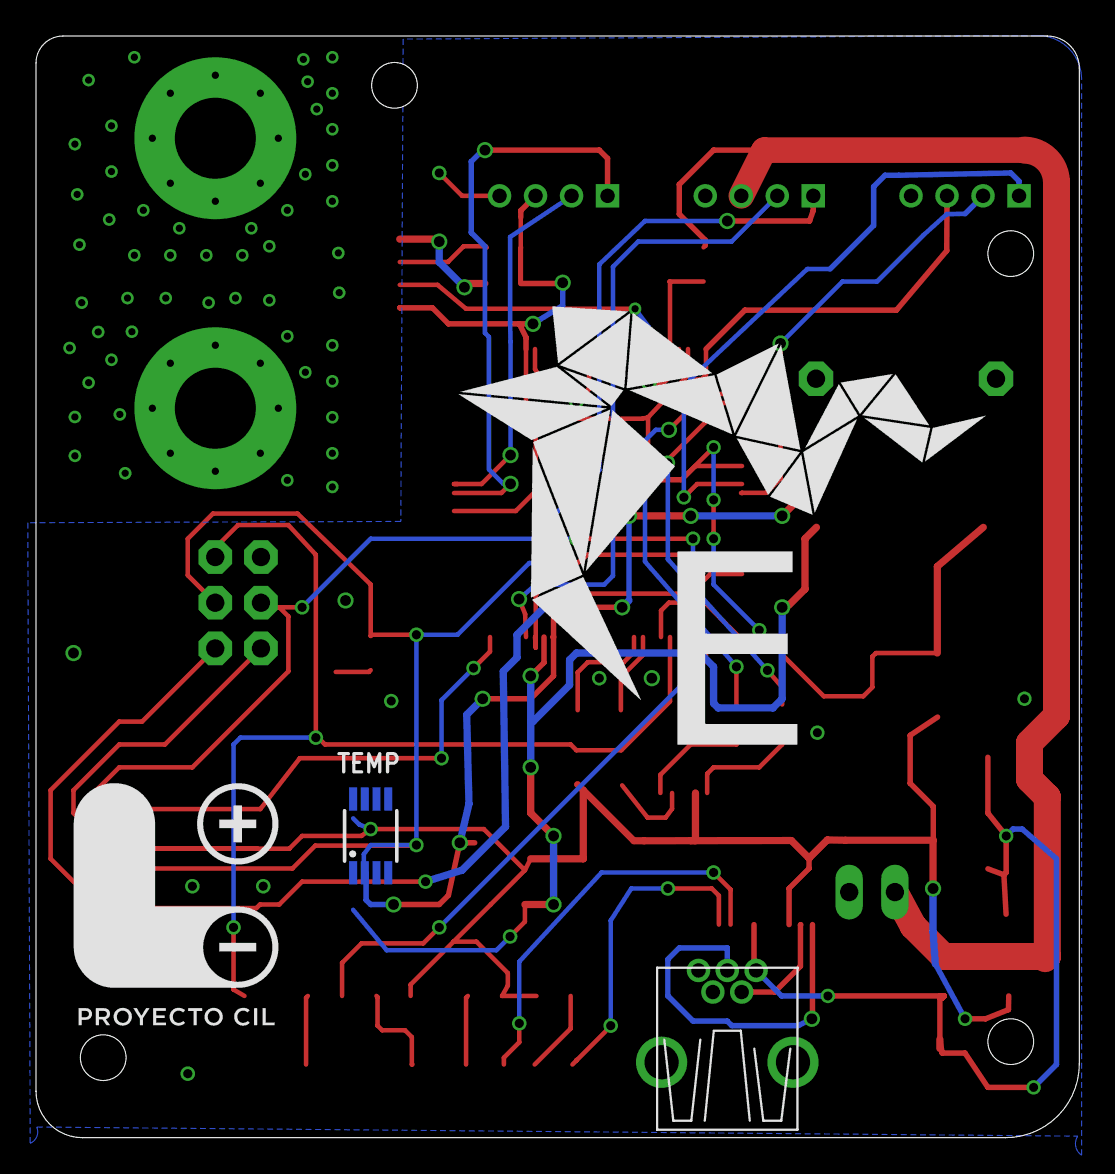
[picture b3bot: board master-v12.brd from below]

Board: 2 copper layers, 58.0 x 61.2 mm, 48 parts (3 on the bottom side), 38 nets.

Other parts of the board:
U$1: LOGO_CIL
U$2: LOGO_ELIBATT
U$4: LOGO_ELIBATT2

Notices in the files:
slave/slave-v10.brd:
Logos Electromechanical (c) 2012
parts and their libraries:
atmel-avr: Copyright (C) 2008, Bob Starr
SparkFun-Connectors: Licensing: Creative Commons ShareAlike 4.0 International - https://creativecommons.org/licenses/by-sa/4.0
SparkFun-Aesthetics: Released under the Creative Commons Attribution Share-Alike 4.0 License
